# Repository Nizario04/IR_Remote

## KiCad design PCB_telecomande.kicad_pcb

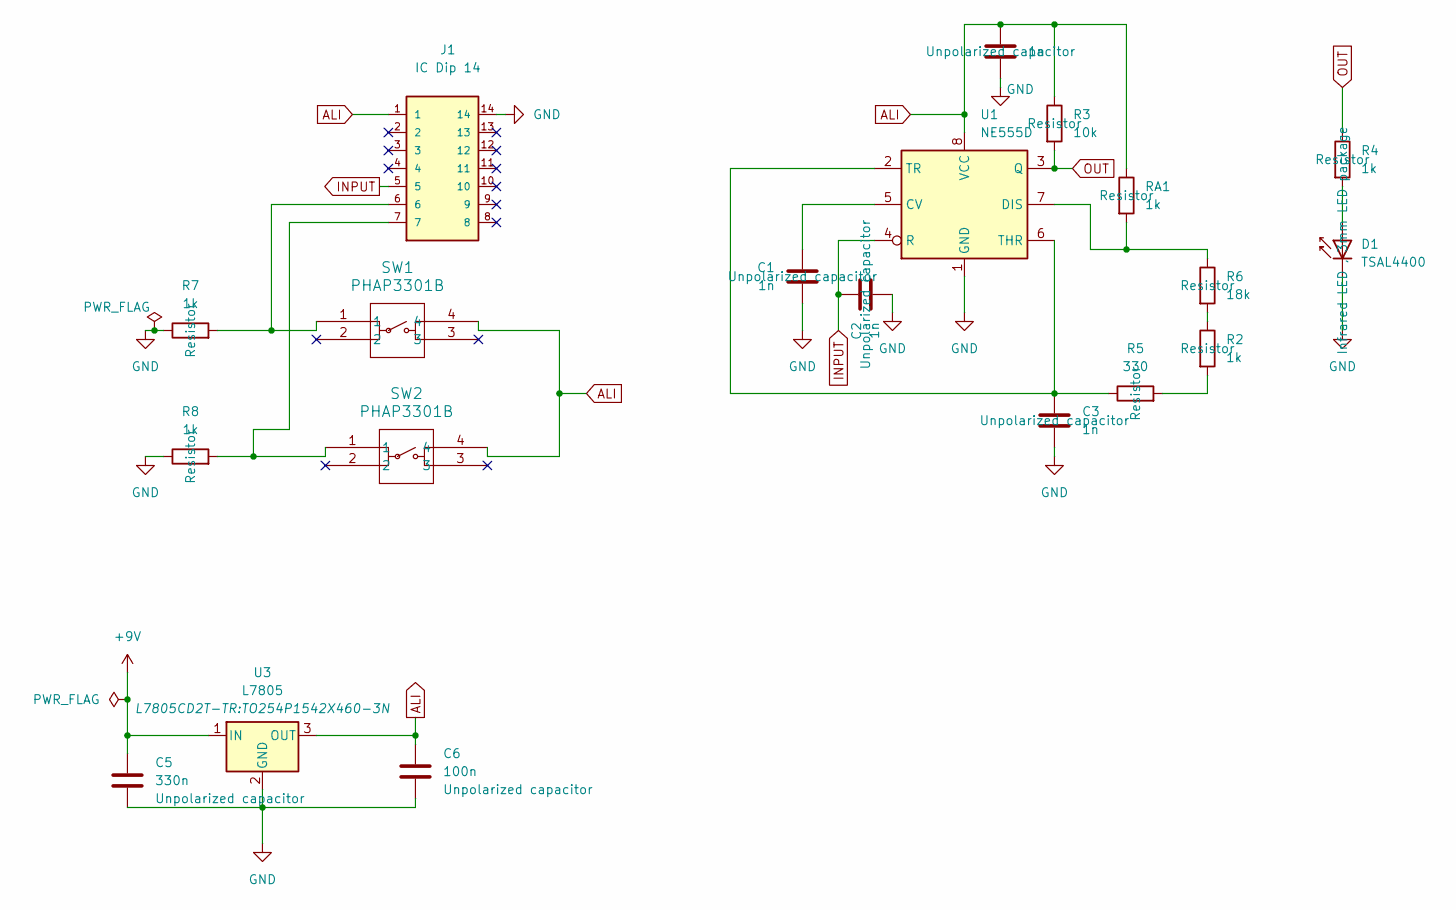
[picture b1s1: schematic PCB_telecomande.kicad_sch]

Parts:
C1, C2, C3, C4: 1n; C_1206_3216Metric_Pad1.33x1.80mm_HandSolder
C5: 330n; C_1206_3216Metric_Pad1.33x1.80mm_HandSolder
C6: 100n; C_1206_3216Metric_Pad1.33x1.80mm_HandSolder
D1: TSAL4400; LED_D3.0mm_IRBlack
J1: IC Dip 14; DIP-14_W7.62mm_Socket; PARTREV A
R2, R4, R7, R8: 1k; R_1206_3216Metric_Pad1.30x1.75mm_HandSolder
R3: 10k; R_1206_3216Metric_Pad1.30x1.75mm_HandSolder
R5: 330; R_1206_3216Metric_Pad1.30x1.75mm_HandSolder
R6: 18k; R_1206_3216Metric_Pad1.30x1.75mm_HandSolder
RA1: 1k; R_1206_3216Metric_Pad1.30x1.75mm_HandSolder
SW1, SW2: PHAP3301B; PHAP3301B_APM
U1: NE555D; SOIC-8_3.9x4.9mm_P1.27mm
U3: L7805; TO254P1542X460-3N

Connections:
+9V: C5.1, U3.1 (IN)
ALI: C4.1, C6.1, J1.1, R3.1, RA1.1, SW1.4, SW2.4, U1.8 (VCC), U3.3 (OUT)
GND: C1.1, C2.1, C3.2, C4.2, C5.2, C6.2, D1.1 (K), J1.14, R7.1, R8.1, U1.1 (GND), U3.2 (GND)
INPUT: C2.2, J1.5, U1.4 (R)
unnamed: D1.2 (A), R4.2
unnamed: J1.6, R7.2, SW1.1
unnamed: J1.7, R8.2, SW2.1
unnamed: R2.1, R6.2
unnamed: R2.2, R5.2
unnamed: C1.2, U1.5 (CV)
unnamed: R6.1, RA1.2, U1.7 (DIS)
unnamed: C3.1, R5.1, U1.2 (TR), U1.6 (THR)
OUT: R3.2, R4.1, U1.3 (Q)

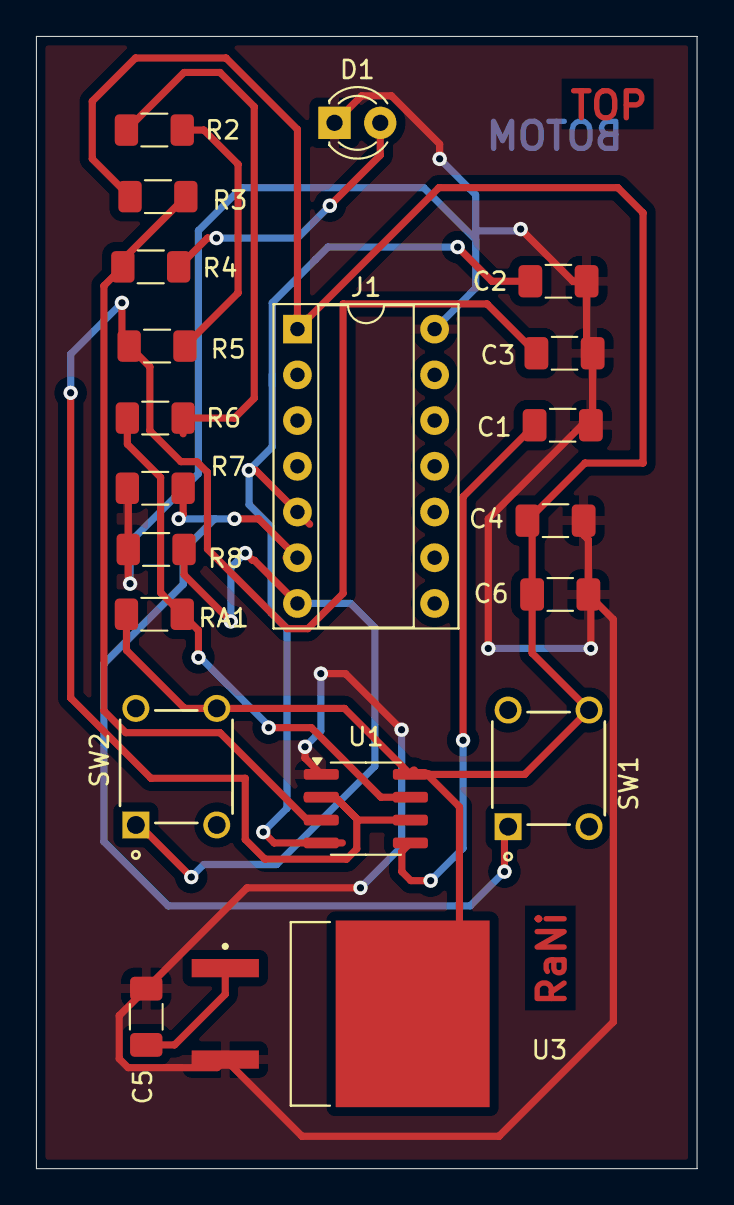
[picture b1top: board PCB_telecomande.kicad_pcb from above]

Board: 2 copper layers, 36.7 x 62.9 mm, 20 parts (0 on the bottom side), 13 nets.
